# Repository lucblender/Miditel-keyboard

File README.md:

# MIDITEL, a MIDI keyboard using a Minitel keyboard

# Description

The Miditel is a Midi keyboard built with a Mini-tel keyboard. The key layout is inspired by an accordion keyboard. Its features are highly inspired by the Arturia Keystep including Normal play, sequencer, or arpeggiator. In addition, it embedded a small Oled screen and give unique a multi-sequencer feature

**The project is based on the MINITEL 1.**

# Hardware

You will need a miditel 1 keyboard with a working keyboard matrix, the PCB which can be found in the [hardware/PCB](hardware/PCB), an 1.3 inch [OLED Display module by waveshare](https://www.waveshare.com/1.3inch-oled-module-c.htm)

# Software

The project run on a raspberry pico 1 with micropython. To this date, it is working under v1.27.0. Download latest micropython image on [Micropython website](https://micropython.org/download/RPI_PICO/).

You then need to transfer .py files and .pbm (pictures) files on the little fs of the pico. All the .py files, all the .pbm files and the folder arp_mode with all its .pbm files.
Here is what the structure should look like.

- arp_mode
  - dwn.pbm
  - dwnx2.pbm
  - ...
- arial6.py
- arial8.py
- arial10.py
- font6.py
- font10.py
- keyboardConfiguration.py
- main.py
- OLED_SPI.py
- writer.py
- lxb64x64.pbm
- pause.pbm
- play.pbm
- rec.pbm
- stop.pbm

## About Minitel

Remove the keyboard from your minitel. You will then connect the ribbon cable of the minitel to a serie of wire and then to J3, the 17 pins connector on the PCB. All the info about the minitel keyboard and its matrix can be found on [entropie.org](https://entropie.org/3615/index.php/2020/08/05/le-clavier-du-minitel-1b/)

## Manufacturing Files

### PCB

The PCB to control the miditel files can be found in the [hardware/PCB](hardware/PCB) folder. I personnaly used [PCBWay](https://www.pcbway.com) service to produce the PCB.

The PCB is as simple double sided PCB.

### Front panel

The manufacturing files of the front panel can be found in the [hardware/FrontPanel](hardware/FrontPanel) folder. It has been made to cnc machine and laser engrave a front panel. They can also be easily converted to make the front panel of a PCB which is a cheaper option.
The Front panel is composed of the following files:

- Top_Platev004 files : the front panel with the cutout
- Top_Plate_design-only : only the "aestetic" part
- Top_Plate_outer_shape : only the "cutout" part

In my original design, the front panel has been made using [PCBWay](https://www.pcbway.com) Sheet Metal Fabrication service. I chose bead-blasted copper with custom laser engraving to fit the color of the Minitel Keyboard.

### 3D printed parts

The manufacturing files of the front panel can be found in the [hardware/3DPrinting](hardware/3DPrinting) folder.

- Bottom_Platev004.3mf : bottom plate that hold the PCB and is glued directly on the minitel
- Wheelv004.3mf : wheel to put on the potentiometers
- paint stencil folder : 3d printable stencil to paint white and black square on the key of the minitel

### LICENSE

[CC BY-NC-SA](https://creativecommons.org/licenses/by-nc-sa/4.0/)

This license enables reusers to distribute, remix, adapt, and build upon the material in any medium or format for noncommercial purposes only, and only so long as attribution is given to the creator. If you remix, adapt, or build upon the material, you must license the modified material under identical terms. CC BY-NC-SA includes the following elements:

BY: credit must be given to the creator.
NC: Only noncommercial uses of the work are permitted.
SA: Adaptations must be shared under the same terms.

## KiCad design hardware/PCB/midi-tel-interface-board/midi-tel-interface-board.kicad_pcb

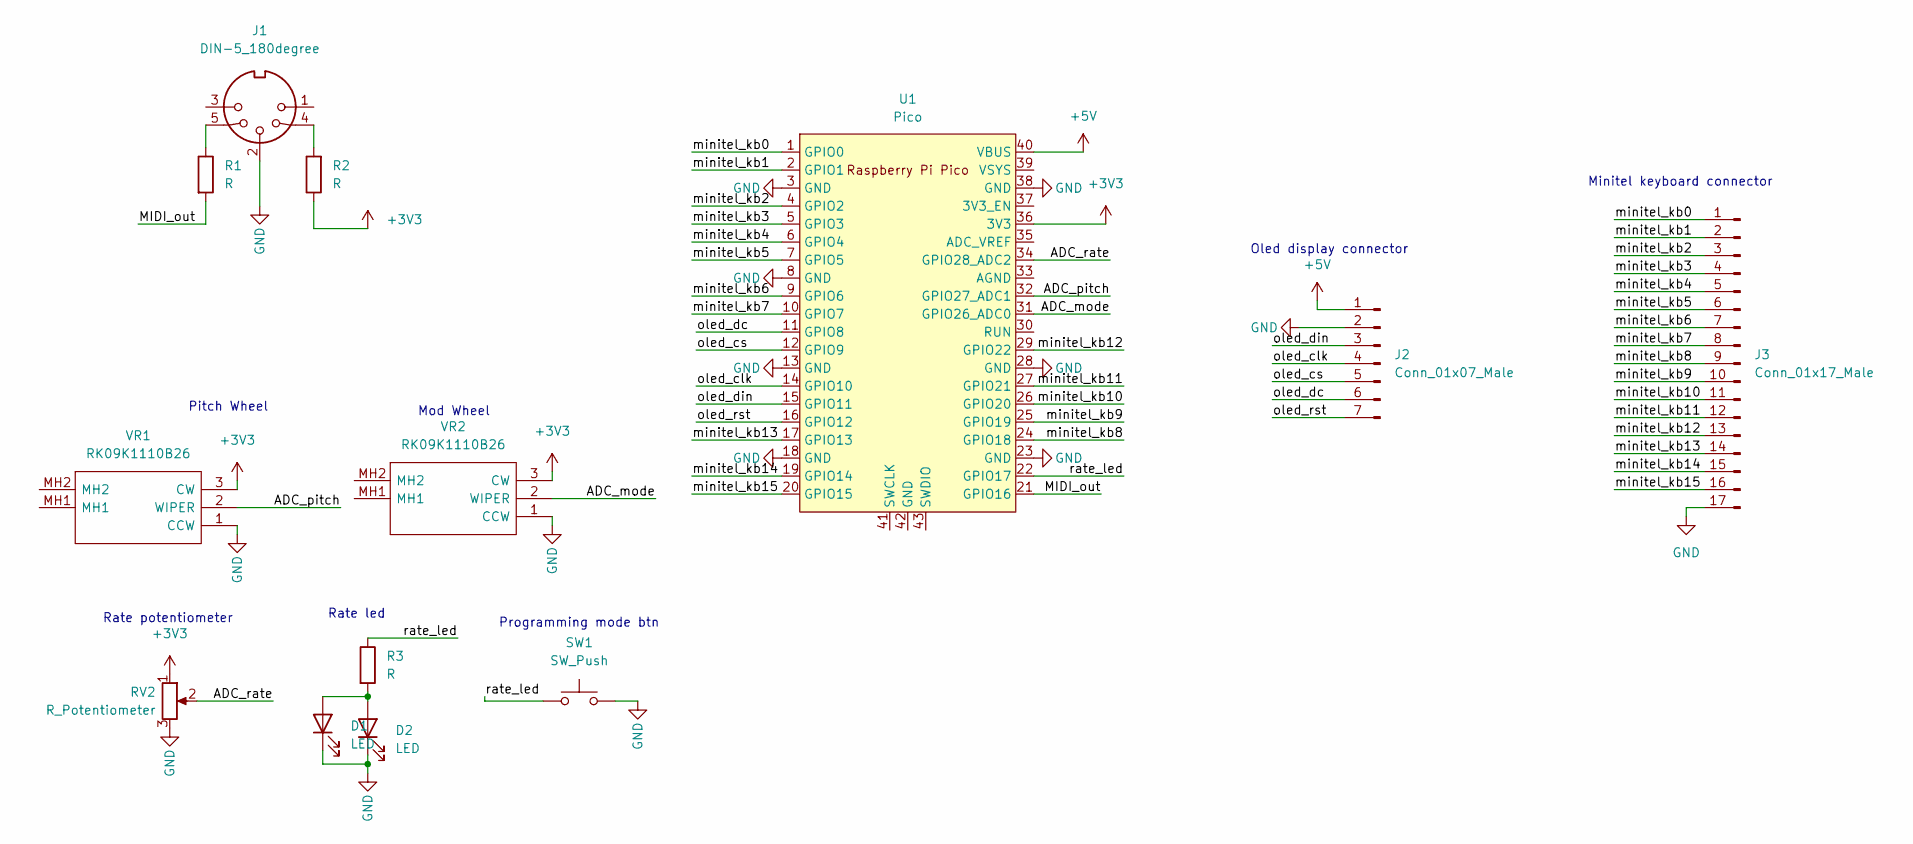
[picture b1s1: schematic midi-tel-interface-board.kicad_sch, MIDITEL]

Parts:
D1: LED; LED_D3.0mm
D2: LED; LED_0603_1608Metric
J1: DIN-5_180degree; 52120441
J2: Conn_01x07_Male; PinHeader_1x07_P2.54mm_Vertical
J3: Conn_01x17_Male; PinHeader_1x17_P2.54mm_Vertical
R1, R2, R3: R; R_0805_2012Metric
RV2: R_Potentiometer; Potentiometer_Alpha_RD901F-40-00D_Single_Vertical
SW1: SW_Push; SW_PUSH_6mm
U1: Pico; RPi_Pico_SMD_TH
VR1, VR2: RK09K1110B26; Mouser Part Number 688-RK09K1110B26

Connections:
+3V3: R2.1, RV2.1, U1.36 (3V3), VR1.3 (CW), VR2.3 (CW)
+5V: J2.1, U1.40 (VBUS)
/ADC_mode: U1.31 (GPIO26_ADC0), VR2.2 (WIPER)
/ADC_pitch: U1.32 (GPIO27_ADC1), VR1.2 (WIPER)
/ADC_rate: RV2.2, U1.34 (GPIO28_ADC2)
/MIDI_out: R1.2, U1.21 (GPIO16)
/minitel_kb0: J3.1, U1.1 (GPIO0)
/minitel_kb1: J3.2, U1.2 (GPIO1)
/minitel_kb2: J3.3, U1.4 (GPIO2)
/minitel_kb3: J3.4, U1.5 (GPIO3)
/minitel_kb4: J3.5, U1.6 (GPIO4)
/minitel_kb5: J3.6, U1.7 (GPIO5)
/minitel_kb6: J3.7, U1.9 (GPIO6)
/minitel_kb7: J3.8, U1.10 (GPIO7)
/minitel_kb8: J3.9, U1.24 (GPIO18)
/minitel_kb9: J3.10, U1.25 (GPIO19)
/minitel_kb10: J3.11, U1.26 (GPIO20)
/minitel_kb11: J3.12, U1.27 (GPIO21)
/minitel_kb12: J3.13, U1.29 (GPIO22)
/minitel_kb13: J3.14, U1.17 (GPIO13)
/minitel_kb14: J3.15, U1.19 (GPIO14)
/minitel_kb15: J3.16, U1.20 (GPIO15)
/oled_clk: J2.4, U1.14 (GPIO10)
/oled_cs: J2.5, U1.12 (GPIO9)
/oled_dc: J2.6, U1.11 (GPIO8)
/oled_din: J2.3, U1.15 (GPIO11)
/oled_rst: J2.7, U1.16 (GPIO12)
/rate_led: R3.1, SW1.1, U1.22 (GPIO17)
GND: D1.1 (K), D2.1 (K), J1.2, J2.2, J3.17, RV2.3, SW1.2, U1.3 (GND), U1.8 (GND), U1.13 (GND), U1.18 (GND), U1.23 (GND), U1.28 (GND), U1.38 (GND), VR1.1 (CCW), VR2.1 (CCW)
unnamed: D1.2 (A), D2.2 (A), R3.2
unnamed: J1.4, R2.2
unnamed: J1.5, R1.1

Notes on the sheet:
Mod Wheel
Oled display connector
Programming mode btn
Rate led
Rate potentiometer
Pitch Wheel
Minitel keyboard connector

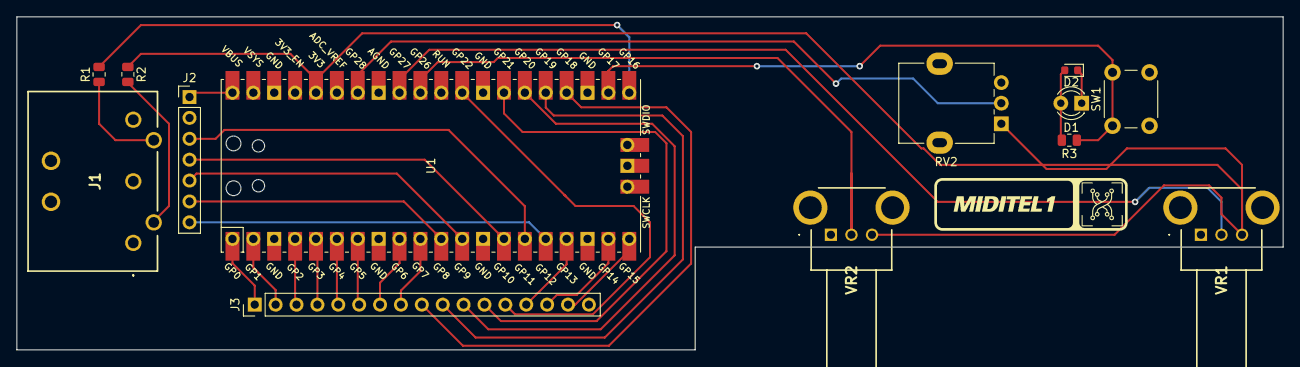
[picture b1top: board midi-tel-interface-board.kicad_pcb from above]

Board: 2 copper layers, 154.0 x 40.5 mm, 13 parts (0 on the bottom side), 32 nets.

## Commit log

2023-01-14 first commit with demo code
2023-01-15 inverted rows and collumn, works better for polyphony + exit button
2023-01-15 start having some parameters and begin of sequencer
2023-01-15 add change of bpm and sequence save and load from files
2023-01-18 simple "order" arpegiator implementation
2023-01-18 added gate length
2023-01-19 add pictures in pbm
2023-01-19 add fonts
2023-01-19 add display 1.3'' oled
2023-01-19 display a message when in programming mode
2023-01-20 start true display of info
2023-01-20 add arp mode picto
2023-01-20 add arpegiator mode only visual
2023-01-21 add arpegiator mode
2023-01-21 add management of time div, add midi clock/stop/resume/play
2023-01-21 add transpose for sequencer and screensaver
2023-01-22 put rate led and reset button on same pin
2023-01-22 add "space" to play 440hz and make possible to play during stop mode
2023-01-22 add kicad pcb
2023-01-22 first rough version of pcb
2023-01-29 add mod and pitch bend wheel
2023-01-29 update gitignore and pcb files
2023-01-31 add error management and start multi-sequencer mode
2023-02-01 add midi for multi-sequence
2023-02-03 add keyboard play in multi_sequencer
2023-02-12 made improvement in the key matrix reading by putting output as 'z'
2023-02-18 put frequency and not period in timer, made timer more stable
2023-02-19 fix typo
2023-02-19 made possible to have longer note in sequencer
2023-02-24 changed way to save sequence
2023-02-24 multisequencer now use new way of saving sequence
2023-05-02 Add readme and first pictures
2023-07-31 fix midi channel and play note when doing sequence recording
2023-07-31 start timediv on multiseq
2023-08-01 reduced refresh of screen due to rate pot
2023-08-01 removed test configuration
2025-11-17 feature: multithreading for screen
2025-11-17 feature: fix screensaver
2025-11-17 fix: auto-indent
2025-11-17 fix: remove unnecessary screensaver setup
2025-11-17 feature: optimization of keyboardConfiguration.
2026-02-15 fix: put 17 pin connectors for keyboard matrix
2026-02-15 feature: add front panel files
2026-02-15 feature: add pictures
2026-02-15 feature: add 3d printing files
2026-02-15 feature: update license
2026-02-15 feature: cleanup doc
